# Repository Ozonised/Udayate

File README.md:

# Udayate
An open source flight controller based on STM32F411 microcontroller.

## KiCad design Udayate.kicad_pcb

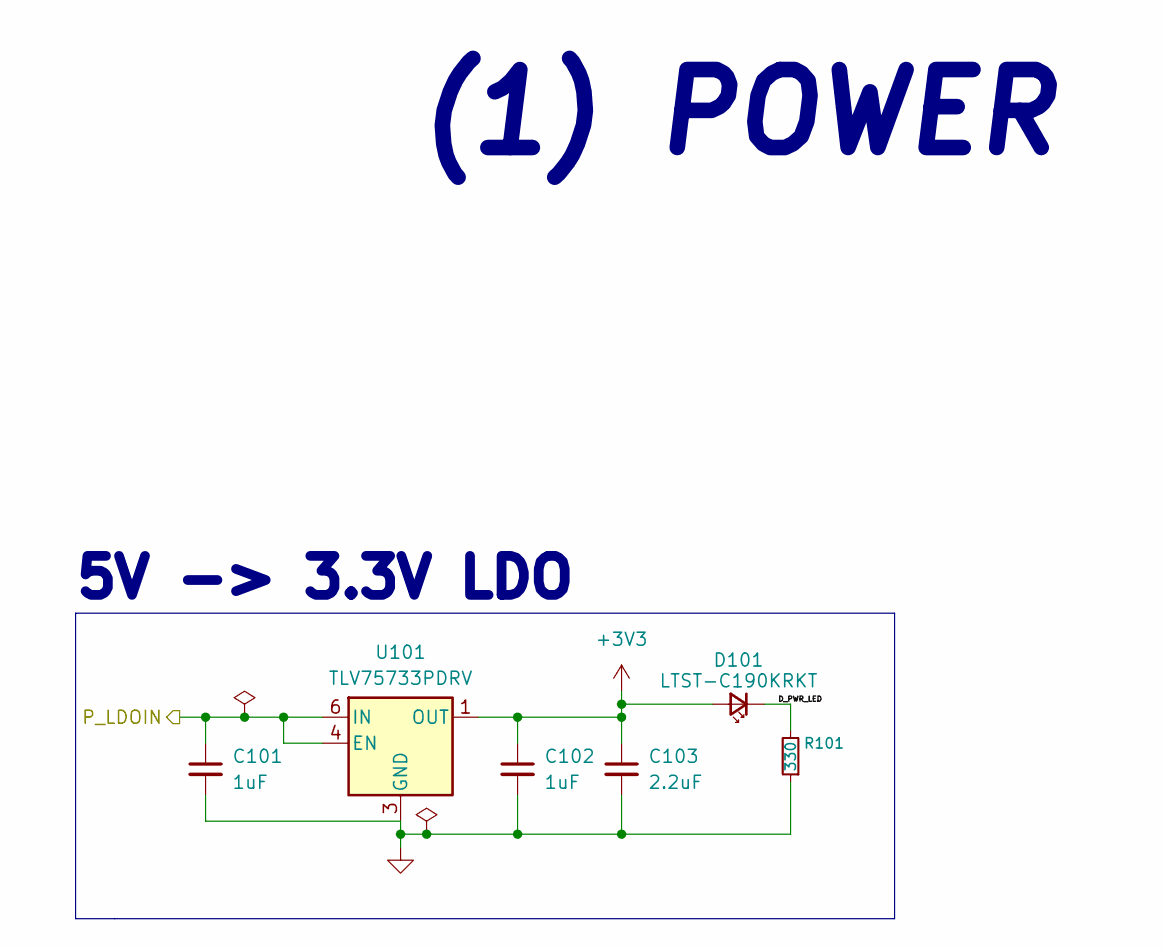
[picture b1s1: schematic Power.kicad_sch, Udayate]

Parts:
C101, C102: 1uF; C_0603_1608Metric_Pad1.08x0.95mm_HandSolder; MPN C1608X7R1V105K080AC
C103: 2.2uF; C_0805_2012Metric_Pad1.18x1.45mm_HandSolder; MPN GCM21BR71C225MA64L
D101: LTST-C190KRKT; LED_0603_1608Metric_Pad1.05x0.95mm_HandSolder; MPN LTST-C190KRKT
R101: 330; R_0603_1608Metric_Pad0.98x0.95mm_HandSolder; MPN CR0603-FX-3300ELF
U101: TLV75733PDRV; WSON-6-1EP_2x2mm_P0.65mm_EP1x1.6mm; MPN TLV75733PDRV

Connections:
+3V3: C102.1, C103.1, D101.2 (A), U101.1 (OUT); also elsewhere on the board
/IO/P_LDOIN: C101.1, U101.4 (EN), U101.6 (IN); also elsewhere on the board
/Power/D_PWR_LED: D101.1 (K), R101.2
GND: C101.2, C102.2, C103.2, R101.1, U101.3 (GND), U101.7 (GND); also elsewhere on the board

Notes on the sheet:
(1) POWER
5V -> 3.3V LDO

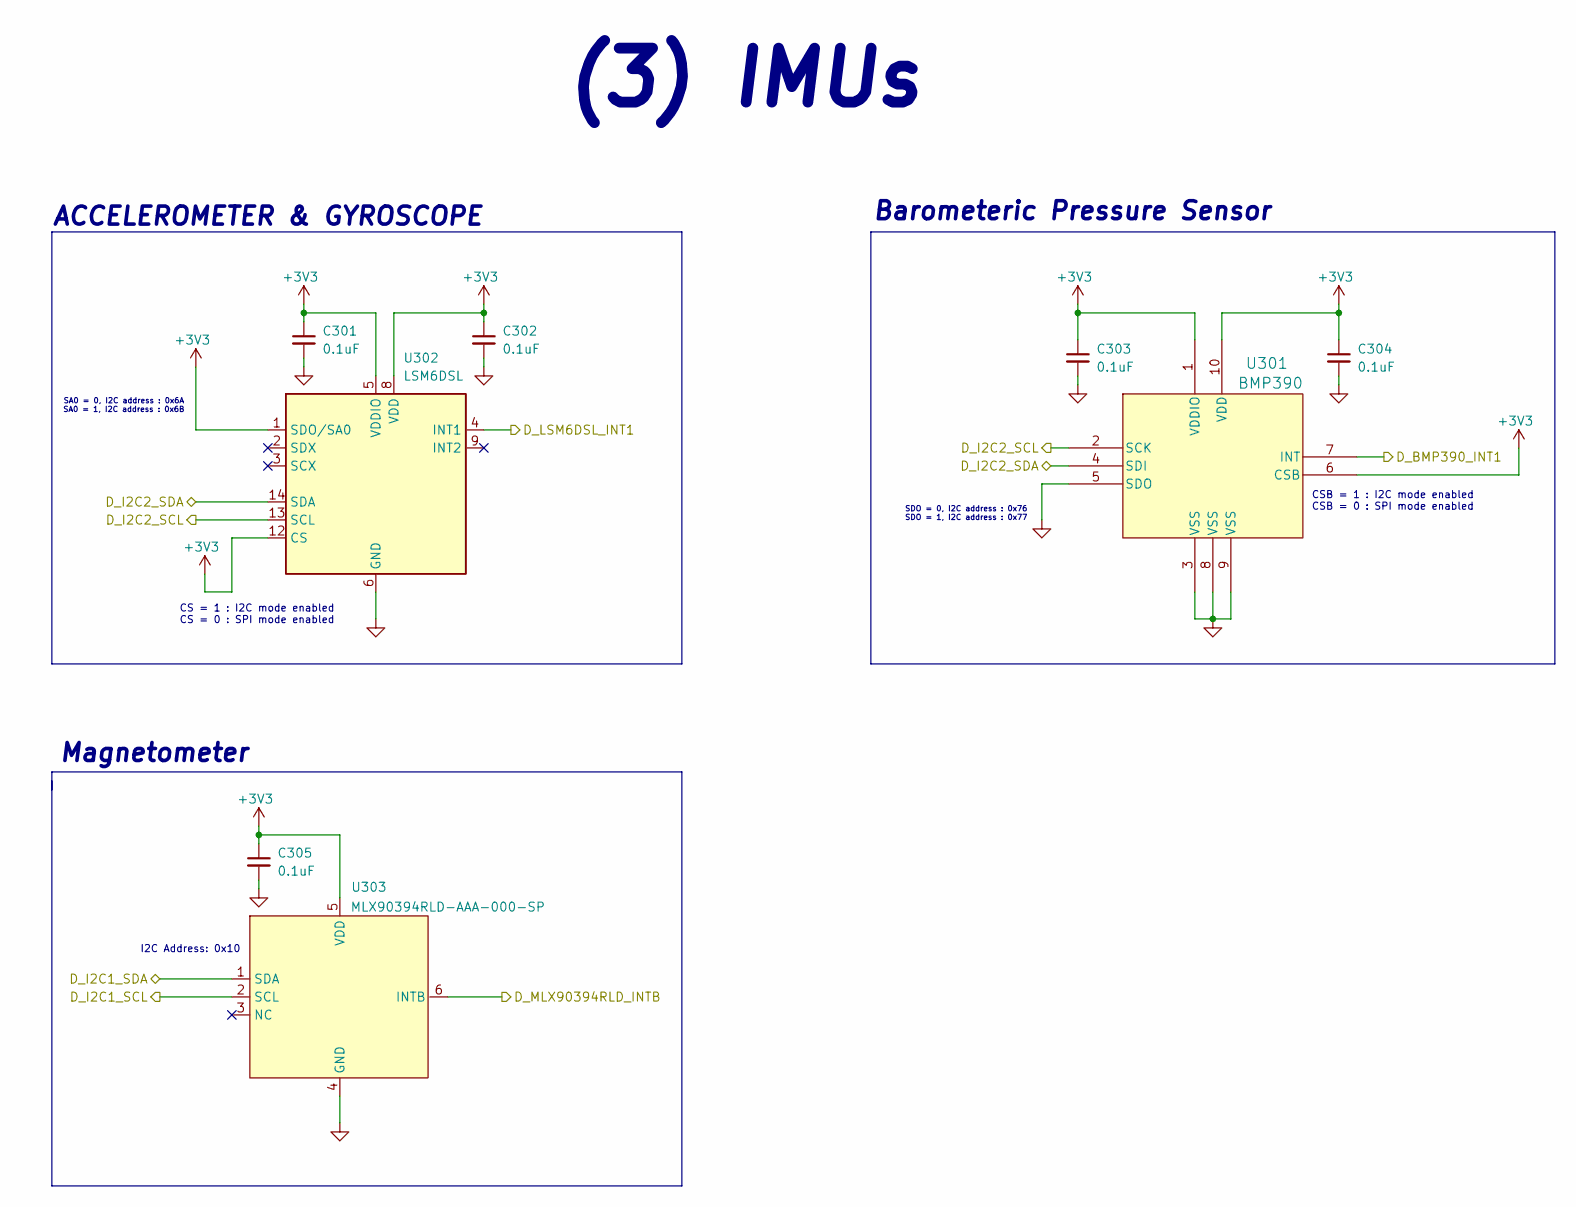
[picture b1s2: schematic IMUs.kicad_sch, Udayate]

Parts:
C301, C302, C303, C304, C305: 0.1uF; C_0603_1608Metric_Pad1.08x0.95mm_HandSolder; MPN C1608X5R1H104K080AA
U301: BMP390; 10LGA_2X2X0p75_BOS; MPN BMP390
U302: LSM6DSL; LGA-14_3x2.5mm_P0.5mm_LayoutBorder3x4y; MPN LSM6DSL
U303: MLX90394RLD-AAA-000-SP; MLX90394RLD; MPN MLX90394RLD-AAA-000-SP

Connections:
+3V3: C301.1, C302.1, C303.1, C304.1, C305.1, U301.1 (VDDIO), U301.6 (CSB), U301.10 (VDD), U302.1 (SDO/SA0), U302.5 (VDDIO), U302.8 (VDD), U302.12 (CS), U303.5 (VDD); also elsewhere on the board
/IMUs/D_BMP390_INT1: U301.7 (INT); also elsewhere on the board
/IMUs/D_I2C1_SCL: U303.2 (SCL); also elsewhere on the board
/IMUs/D_I2C1_SDA: U303.1 (SDA); also elsewhere on the board
/IMUs/D_I2C2_SCL: U301.2 (SCK), U302.13 (SCL); also elsewhere on the board
/IMUs/D_I2C2_SDA: U301.4 (SDI), U302.14 (SDA); also elsewhere on the board
/IMUs/D_LSM6DSL_INT1: U302.4 (INT1); also elsewhere on the board
/IMUs/D_MLX90394RLD_INTB: U303.6 (INTB); also elsewhere on the board
GND: C301.2, C302.2, C303.2, C304.2, C305.2, U301.3 (VSS), U301.5 (SDO), U301.8 (VSS), U301.9 (VSS), U302.6 (GND), U302.7 (GND), U303.4 (GND); also elsewhere on the board

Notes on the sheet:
CSB = 1 : I2C mode enabled CSB = 0 : SPI mode enabled
(3) IMUs
Magnetometer
SDO = 0, I2C address : 0x76 SDO = 1, I2C address : 0x77
SA0 = 0, I2C address : 0x6A SA0 = 1, I2C address : 0x6B
CS = 1 : I2C mode enabled CS = 0 : SPI mode enabled
I2C Address: 0x10
Barometeric Pressure Sensor
ACCELEROMETER & GYROSCOPE

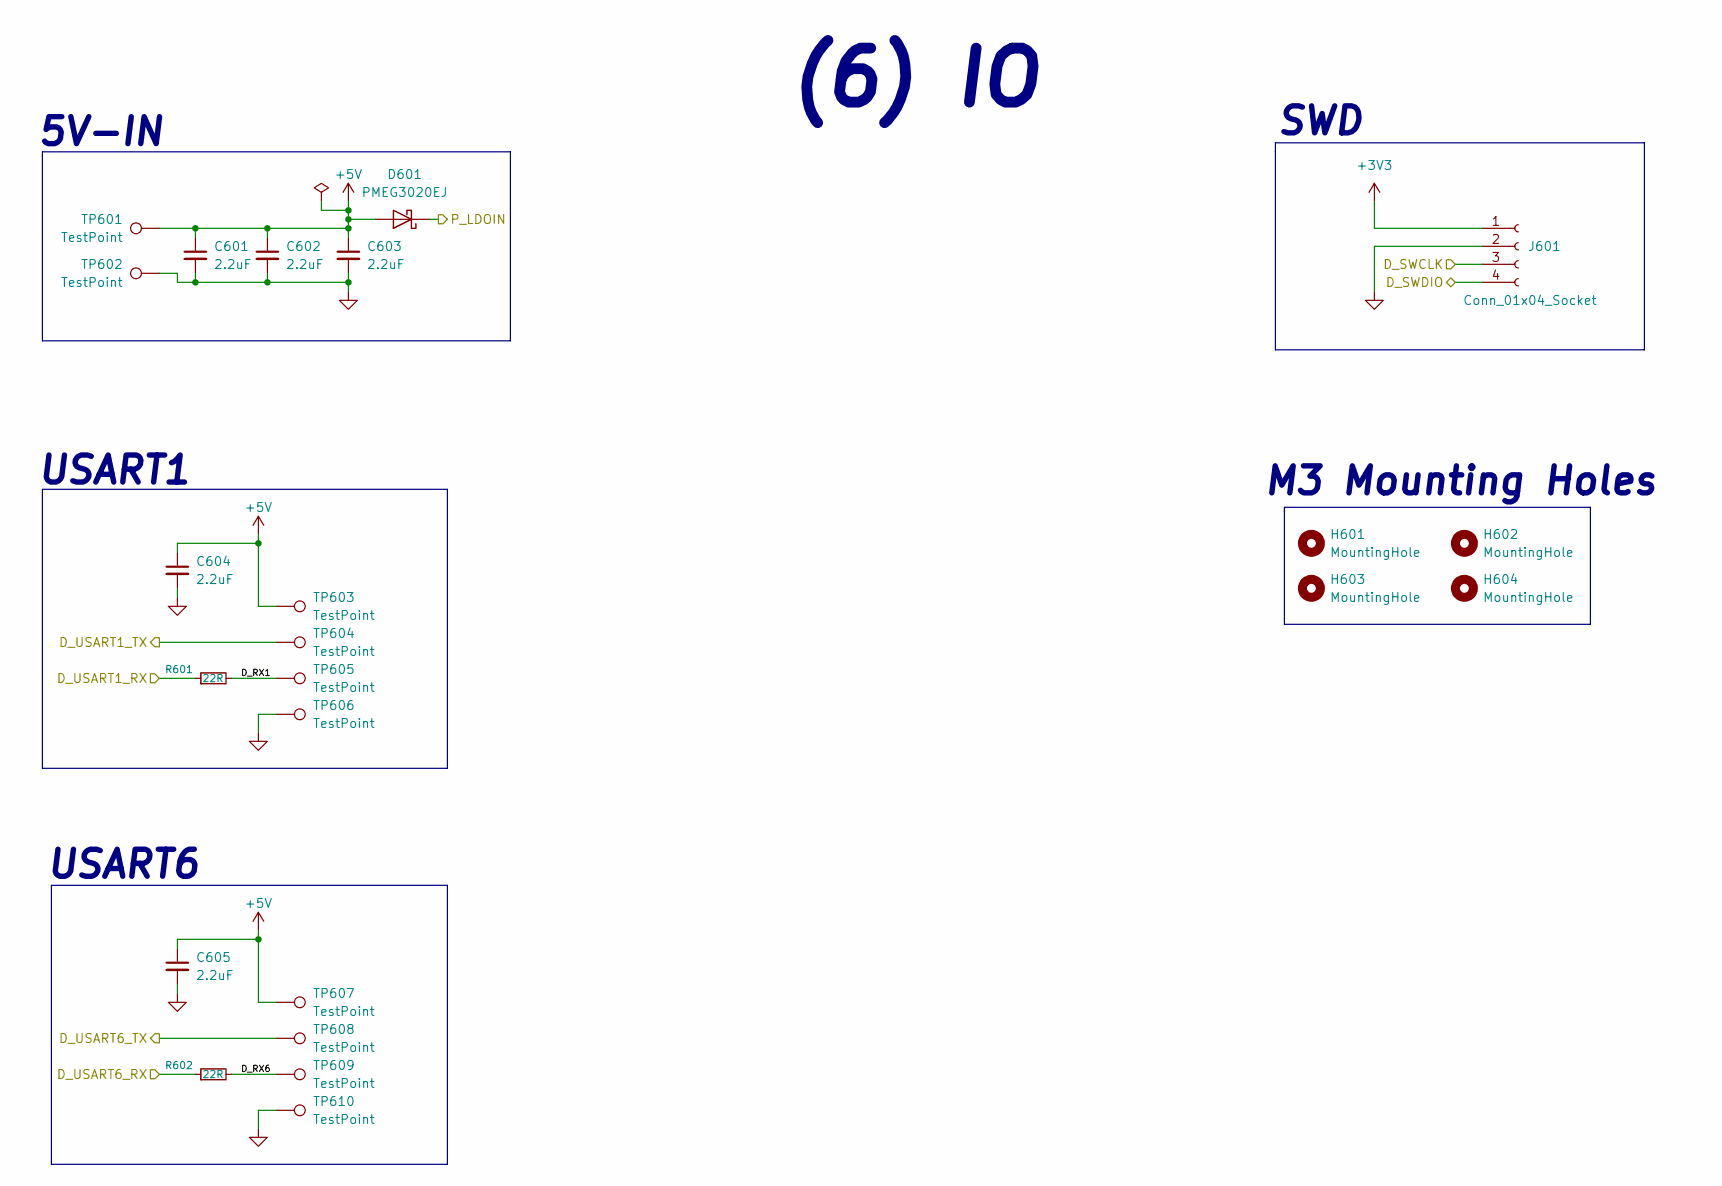
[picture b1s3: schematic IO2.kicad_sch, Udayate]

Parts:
C601, C602, C603, C604, C605: 2.2uF; C_0805_2012Metric_Pad1.18x1.45mm_HandSolder; MPN GCM21BR71C225MA64L
D601: PMEG3020EJ; D_SOD-323F; MPN PMEG3020EJ,115
H601, H602, H603, H604: MountingHole; MountingHole_3.2mm_M3
J601: Conn_01x04_Socket; PinHeader_1x04_P2.54mm_Vertical
R601, R602: 22R; R_0603_1608Metric_Pad0.98x0.95mm_HandSolder; MPN CR0603-FX-22R0ELF
TP601, TP602: TestPoint; TestPoint_Pad_2.0x2.0mm
TP603, TP604, TP605, TP606, TP607, TP608, TP609, TP610: TestPoint; TestPoint_Pad_1.0x1.0mm

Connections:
+3V3: J601.1; also elsewhere on the board
+5V: C601.1, C602.1, C603.1, C604.1, C605.1, D601.2 (A), TP601.1, TP603.1, TP607.1; also elsewhere on the board
/IO2/D_RX1: R601.2, TP605.1
/IO2/D_RX6: R602.2, TP609.1
/IO2/D_SWCLK: J601.3; also elsewhere on the board
/IO2/D_SWDIO: J601.4; also elsewhere on the board
/IO2/D_USART1_RX: R601.1; also elsewhere on the board
/IO2/D_USART1_TX: TP604.1; also elsewhere on the board
/IO2/D_USART6_RX: R602.1; also elsewhere on the board
/IO2/D_USART6_TX: TP608.1; also elsewhere on the board
/IO/P_LDOIN: D601.1 (K); also elsewhere on the board
GND: C601.2, C602.2, C603.2, C604.2, C605.2, J601.2, TP602.1, TP606.1, TP610.1; also elsewhere on the board

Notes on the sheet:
5V-IN
USART1
(6) IO
SWD
USART6
M3 Mounting Holes

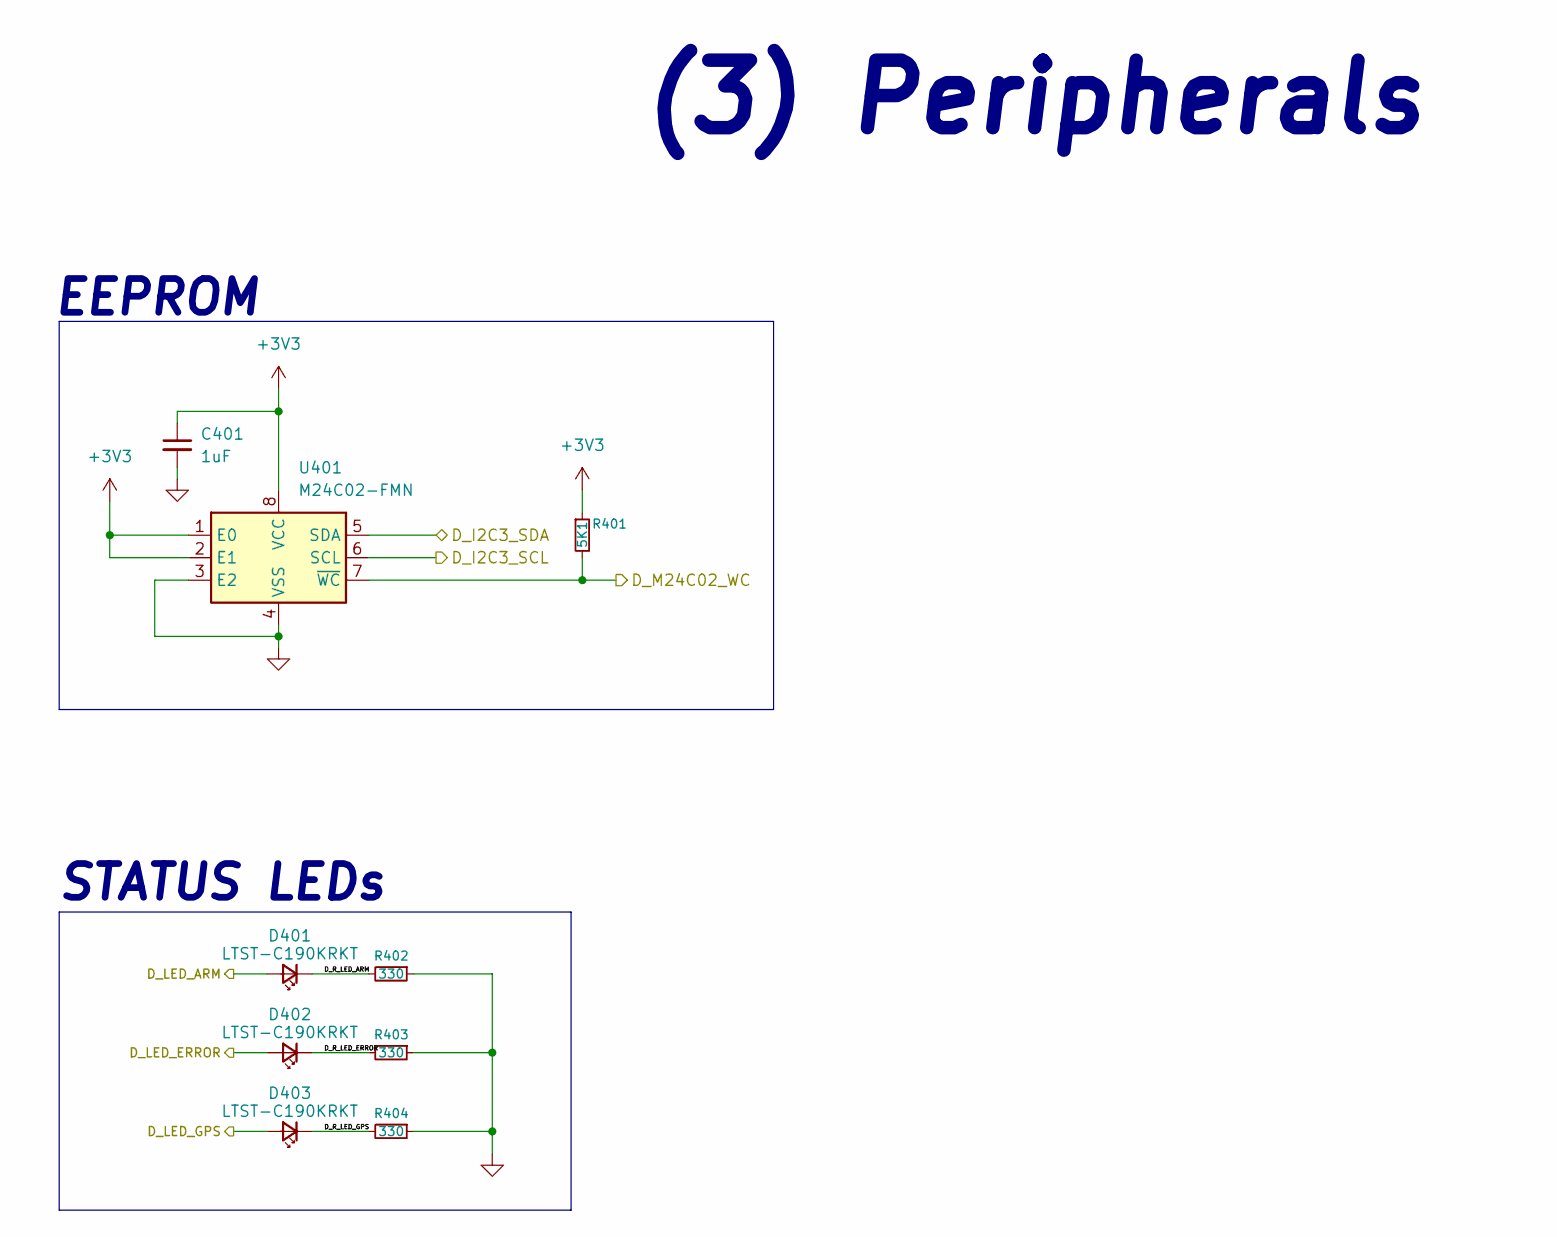
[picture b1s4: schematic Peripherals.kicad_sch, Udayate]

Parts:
C401: 1uF; C_0603_1608Metric_Pad1.08x0.95mm_HandSolder; MPN C1608X7R1V105K080AC
D401, D402, D403: LTST-C190KRKT; LED_0603_1608Metric_Pad1.05x0.95mm_HandSolder; MPN LTST-C190KRKT
R401: 5K1; R_0603_1608Metric_Pad0.98x0.95mm_HandSolder; MPN CR0603-FX-5101ELF
R402, R403, R404: 330; R_0603_1608Metric_Pad0.98x0.95mm_HandSolder; MPN CR0603-FX-3300ELF
U401: M24C02-FMN; SOIC-8_3.9x4.9mm_P1.27mm; MPN M24C02-FMN6TP

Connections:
+3V3: C401.1, R401.1, U401.1 (E0), U401.2 (E1), U401.8 (VCC); also elsewhere on the board
/MCU/D_I2C3_SCL: U401.6 (SCL); also elsewhere on the board
/MCU/D_I2C3_SDA: U401.5 (SDA); also elsewhere on the board
/MCU/D_LED_ARM: D401.2 (A); also elsewhere on the board
/MCU/D_LED_ERROR: D402.2 (A); also elsewhere on the board
/MCU/D_LED_GPS: D403.2 (A); also elsewhere on the board
/MCU/D_M24C02_WC: R401.2, U401.7 (~WC); also elsewhere on the board
/Peripherals/D_R_LED_ARM: D401.1 (K), R402.2
/Peripherals/D_R_LED_ERROR: D402.1 (K), R403.2
/Peripherals/D_R_LED_GPS: D403.1 (K), R404.2
GND: C401.2, R402.1, R403.1, R404.1, U401.3 (E2), U401.4 (VSS); also elsewhere on the board

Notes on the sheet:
(3) Peripherals
STATUS LEDs
EEPROM

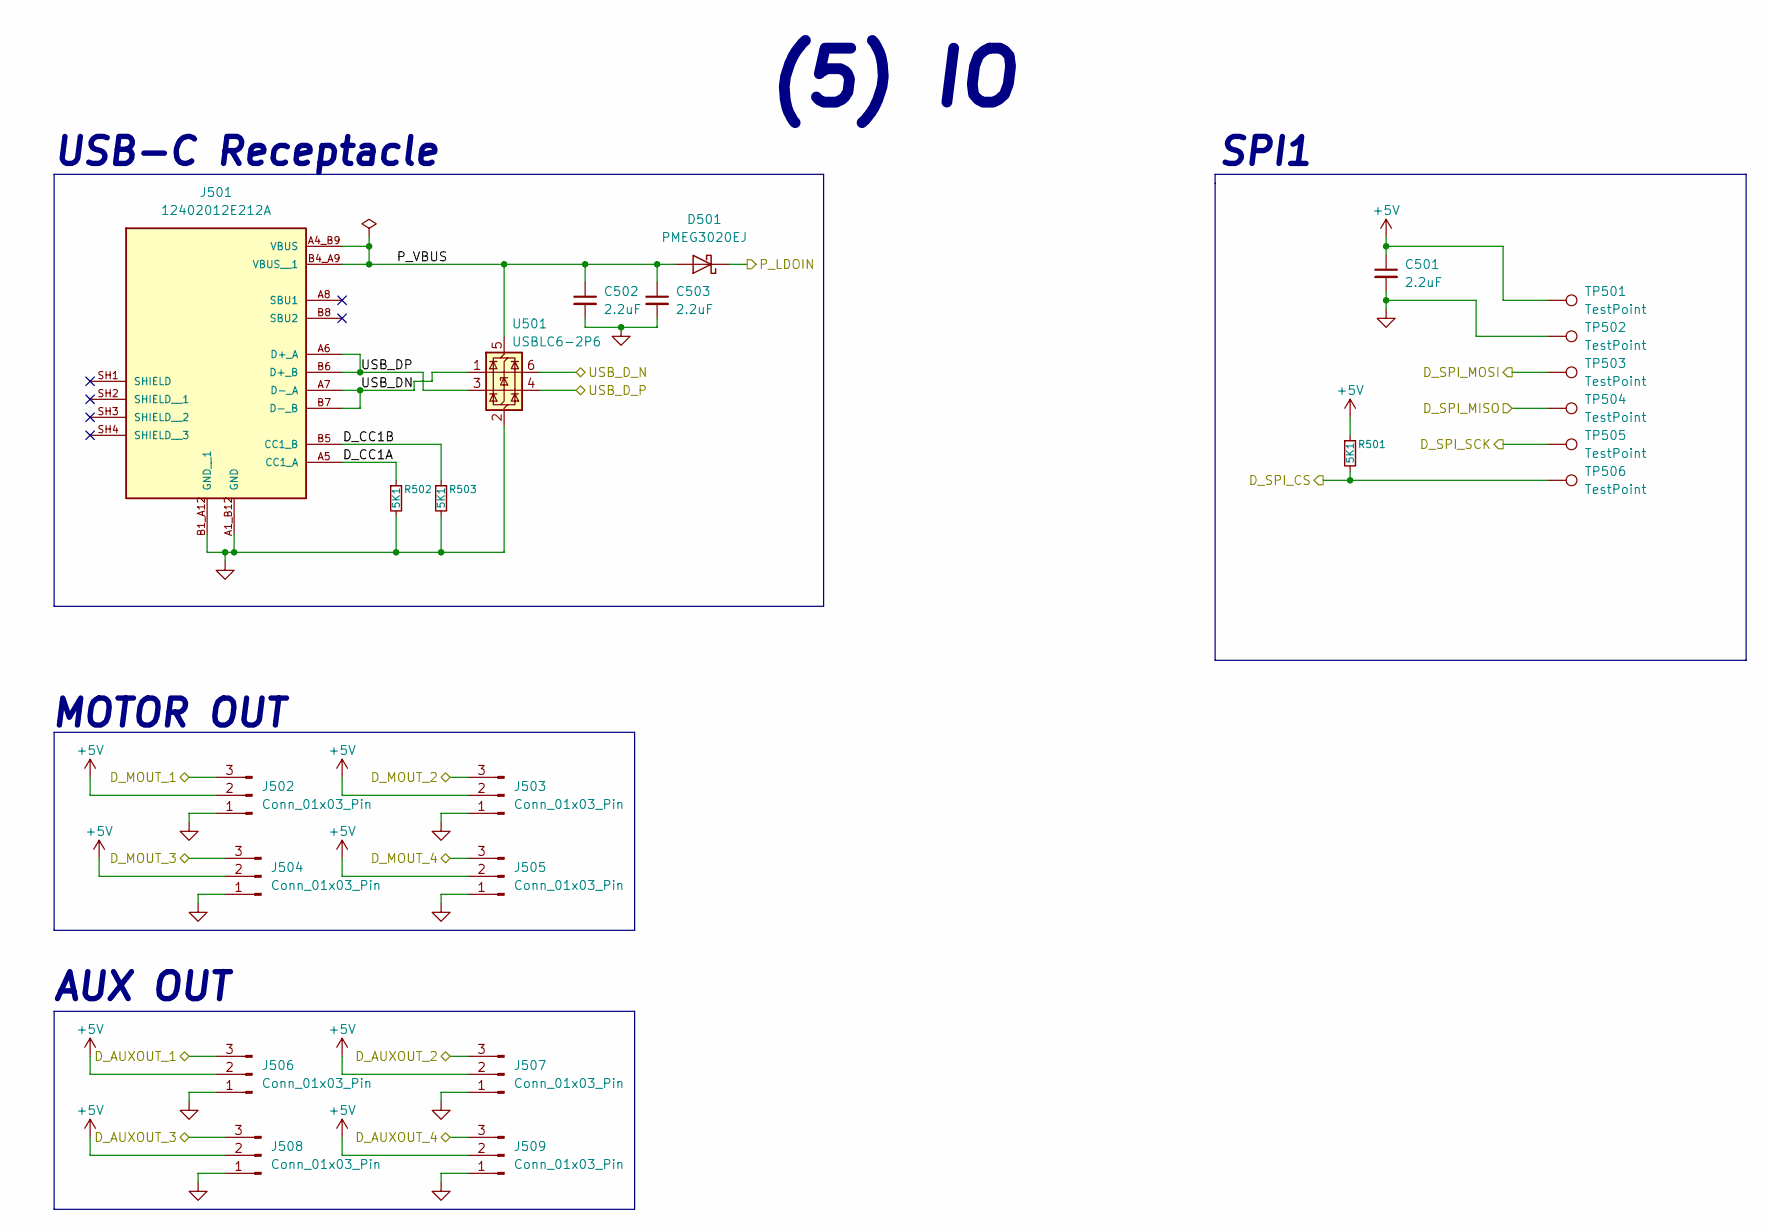
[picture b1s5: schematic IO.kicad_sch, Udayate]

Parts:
C501, C502, C503: 2.2uF; C_0805_2012Metric_Pad1.18x1.45mm_HandSolder; MPN GCM21BR71C225MA64L
D501: PMEG3020EJ; D_SOD-323F; MPN PMEG3020EJ,115
J501: 12402012E212A; AMPHENOL_12402012E212A; PARTREV 4
J502, J503, J504, J505, J506, J507, J508, J509: Conn_01x03_Pin; PinHeader_1x03_P2.54mm_Vertical
R501, R502, R503: 5K1; R_0603_1608Metric_Pad0.98x0.95mm_HandSolder; MPN CR0603-FX-5101ELF
TP501, TP502, TP503, TP504, TP505, TP506: TestPoint; TestPoint_Pad_1.0x1.0mm
U501: USBLC6-2P6; SOT-666

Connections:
+5V: C501.1, J502.2, J503.2, J504.2, J505.2, J506.2, J507.2, J508.2, J509.2, R501.1, TP501.1; also elsewhere on the board
/IO/D_AUXOUT_1: J506.3; also elsewhere on the board
/IO/D_AUXOUT_2: J507.3; also elsewhere on the board
/IO/D_AUXOUT_3: J508.3; also elsewhere on the board
/IO/D_AUXOUT_4: J509.3; also elsewhere on the board
/IO/D_CC1A: J501.A5 (CC1_A), R502.1
/IO/D_CC1B: J501.B5 (CC1_B), R503.1
/IO/D_MOUT_1: J502.3; also elsewhere on the board
/IO/D_MOUT_2: J503.3; also elsewhere on the board
/IO/D_MOUT_3: J504.3; also elsewhere on the board
/IO/D_MOUT_4: J505.3; also elsewhere on the board
/IO/D_SPI_CS: R501.2, TP506.1; also elsewhere on the board
/IO/D_SPI_MISO: TP504.1; also elsewhere on the board
/IO/D_SPI_MOSI: TP503.1; also elsewhere on the board
/IO/D_SPI_SCK: TP505.1; also elsewhere on the board
/IO/P_LDOIN: D501.1 (K); also elsewhere on the board
/IO/P_VBUS: C502.1, C503.1, D501.2 (A), J501.A4_B9 (VBUS), J501.B4_A9 (VBUS__1), U501.5 (VBUS)
/IO/USB_DN: J501.A7 (D-_A), J501.B7 (D-_B), U501.1 (I/O1)
/IO/USB_DP: J501.A6 (D+_A), J501.B6 (D+_B), U501.3 (I/O2)
/IO/USB_D_N: U501.6 (I/O1); also elsewhere on the board
/IO/USB_D_P: U501.4 (I/O2); also elsewhere on the board
GND: C501.2, C502.2, C503.2, J501.A1_B12 (GND), J501.B1_A12 (GND__1), J502.1, J503.1, J504.1, J505.1, J506.1, J507.1, J508.1, J509.1, R502.2, R503.2, TP502.1, U501.2 (GND); also elsewhere on the board

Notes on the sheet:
MOTOR OUT
SPI1
USB-C Receptacle
(5) IO
AUX OUT

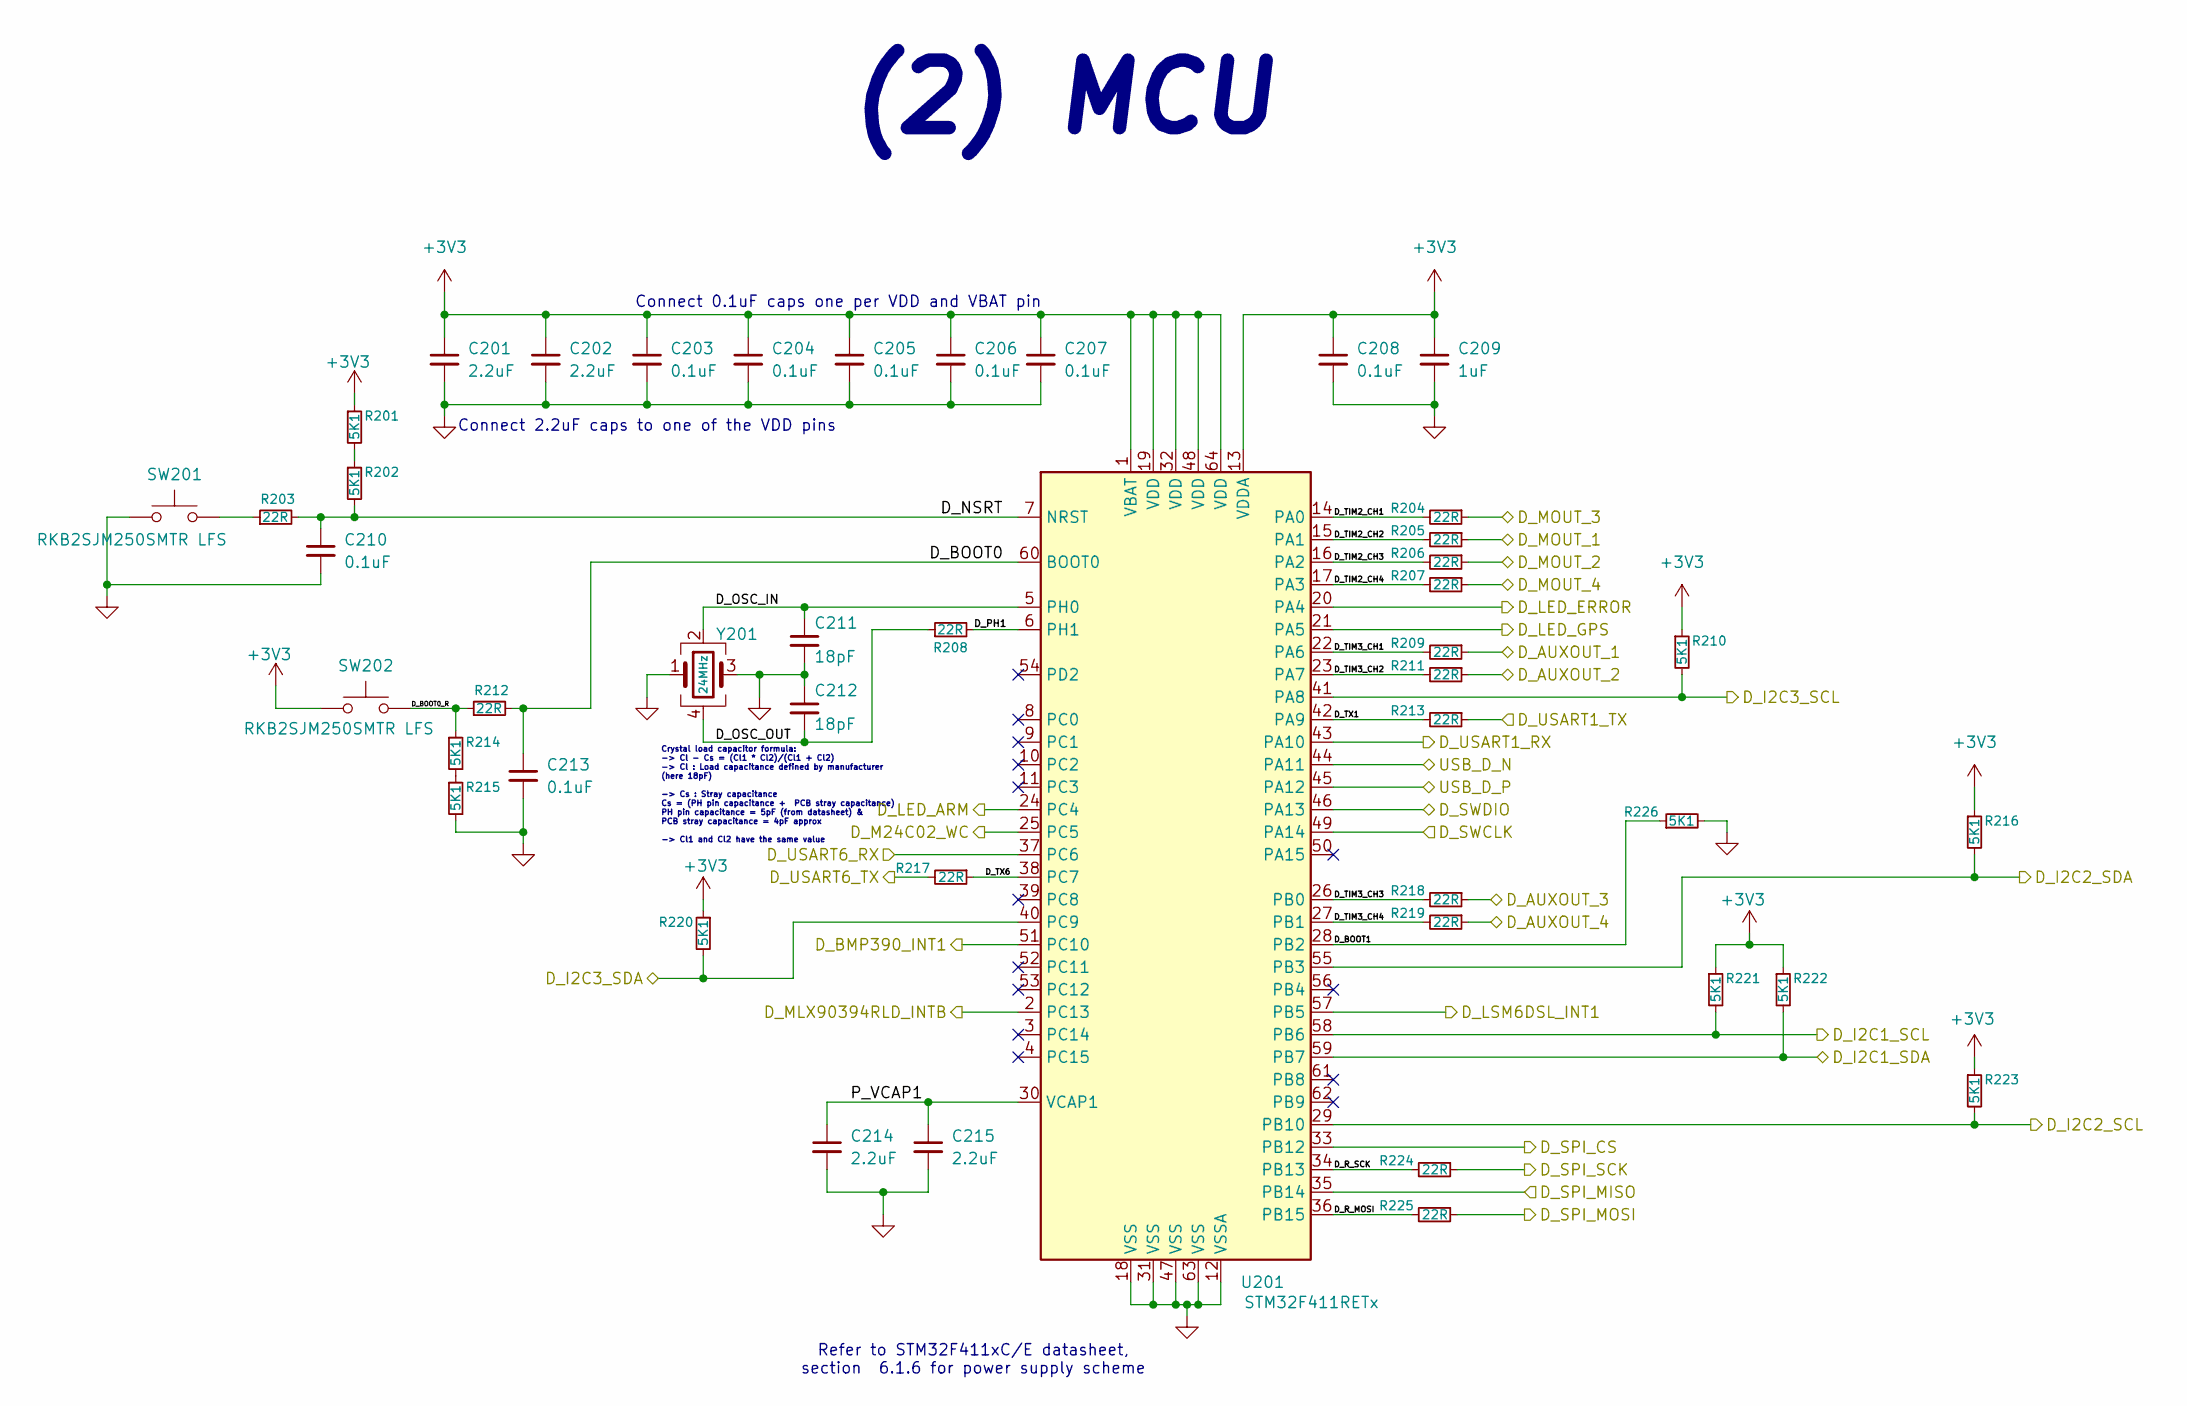
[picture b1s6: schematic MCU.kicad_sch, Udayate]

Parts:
C201, C202, C214, C215: 2.2uF; C_0805_2012Metric_Pad1.18x1.45mm_HandSolder; MPN GCM21BR71C225MA64L
C203, C204, C205, C206, C207, C208, C210, C213: 0.1uF; C_0603_1608Metric_Pad1.08x0.95mm_HandSolder; MPN C1608X5R1H104K080AA
C209: 1uF; C_0603_1608Metric_Pad1.08x0.95mm_HandSolder; MPN C1608X7R1V105K080AC
C211, C212: 18pF; C_0603_1608Metric_Pad1.08x0.95mm_HandSolder; MPN 06035A180JAT4A
R201, R202, R210, R214, R215, R216, R220, R221, R222, R223, R226: 5K1; R_0603_1608Metric_Pad0.98x0.95mm_HandSolder; MPN CR0603-FX-5101ELF
R203, R204, R205, R206, R207, R208, R209, R211, R212, R213, R217, R218, R219, R224, R225: 22R; R_0603_1608Metric_Pad0.98x0.95mm_HandSolder; MPN CR0603-FX-22R0ELF
SW201, SW202: RKB2SJM250SMTR LFS; SW_SPST_PTS810; MPN RKB2SJM250SMTR LFS
U201: STM32F411RETx; LQFP-64_10x10mm_P0.5mm; MPN STM32F411RET6
Y201: 24MHz; Crystal_SMD_3225-4Pin_3.2x2.5mm_HandSoldering; MPN ABM8-24.000MHZ-D4Y-T

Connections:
+3V3: C201.1, C202.1, C203.1, C204.1, C205.1, C206.1, C207.1, C208.1, C209.1, R201.1, R210.1, R216.1, R220.1, R221.1, R222.1, R223.1, SW202.1, U201.1 (VBAT), U201.13 (VDDA), U201.19 (VDD), U201.32 (VDD), U201.48 (VDD), U201.64 (VDD); also elsewhere on the board
/IMUs/D_BMP390_INT1: U201.51 (PC10); also elsewhere on the board
/IMUs/D_I2C1_SCL: R221.2, U201.58 (PB6); also elsewhere on the board
/IMUs/D_I2C1_SDA: R222.2, U201.59 (PB7); also elsewhere on the board
/IMUs/D_I2C2_SCL: R223.2, U201.29 (PB10); also elsewhere on the board
/IMUs/D_I2C2_SDA: R216.2, U201.55 (PB3); also elsewhere on the board
/IMUs/D_LSM6DSL_INT1: U201.57 (PB5); also elsewhere on the board
/IMUs/D_MLX90394RLD_INTB: U201.2 (PC13); also elsewhere on the board
/IO2/D_SWCLK: U201.49 (PA14); also elsewhere on the board
/IO2/D_SWDIO: U201.46 (PA13); also elsewhere on the board
/IO2/D_USART1_RX: U201.43 (PA10); also elsewhere on the board
/IO2/D_USART1_TX: R213.1; also elsewhere on the board
/IO2/D_USART6_RX: U201.37 (PC6); also elsewhere on the board
/IO2/D_USART6_TX: R217.2; also elsewhere on the board
/IO/D_AUXOUT_1: R209.1; also elsewhere on the board
/IO/D_AUXOUT_2: R211.1; also elsewhere on the board
/IO/D_AUXOUT_3: R218.1; also elsewhere on the board
/IO/D_AUXOUT_4: R219.1; also elsewhere on the board
/IO/D_MOUT_1: R205.1; also elsewhere on the board
/IO/D_MOUT_2: R206.1; also elsewhere on the board
/IO/D_MOUT_3: R204.1; also elsewhere on the board
/IO/D_MOUT_4: R207.1; also elsewhere on the board
/IO/D_SPI_CS: U201.33 (PB12); also elsewhere on the board
/IO/D_SPI_MISO: U201.35 (PB14); also elsewhere on the board
/IO/D_SPI_MOSI: R225.1; also elsewhere on the board
/IO/D_SPI_SCK: R224.1; also elsewhere on the board
/IO/USB_D_N: U201.44 (PA11); also elsewhere on the board
/IO/USB_D_P: U201.45 (PA12); also elsewhere on the board
/MCU/D_BOOT0: C213.1, R212.2, U201.60 (BOOT0)
/MCU/D_BOOT0_R: R212.1, R214.1, SW202.2
/MCU/D_BOOT1: R226.1, U201.28 (PB2)
/MCU/D_I2C3_SCL: R210.2, U201.41 (PA8); also elsewhere on the board
/MCU/D_I2C3_SDA: R220.2, U201.40 (PC9); also elsewhere on the board
/MCU/D_LED_ARM: U201.24 (PC4); also elsewhere on the board
/MCU/D_LED_ERROR: U201.20 (PA4); also elsewhere on the board
/MCU/D_LED_GPS: U201.21 (PA5); also elsewhere on the board
/MCU/D_M24C02_WC: U201.25 (PC5); also elsewhere on the board
/MCU/D_NSRT: C210.1, R202.2, R203.2, U201.7 (NRST)
/MCU/D_OSC_IN: C211.1, U201.5 (PH0), Y201.2
/MCU/D_OSC_OUT: C212.2, R208.1, Y201.4
/MCU/D_PH1: R208.2, U201.6 (PH1)
/MCU/D_R_MOSI: R225.2, U201.36 (PB15)
/MCU/D_R_SCK: R224.2, U201.34 (PB13)
/MCU/D_TIM2_CH1: R204.2, U201.14 (PA0)
/MCU/D_TIM2_CH2: R205.2, U201.15 (PA1)
/MCU/D_TIM2_CH3: R206.2, U201.16 (PA2)
/MCU/D_TIM2_CH4: R207.2, U201.17 (PA3)
/MCU/D_TIM3_CH1: R209.2, U201.22 (PA6)
/MCU/D_TIM3_CH2: R211.2, U201.23 (PA7)
/MCU/D_TIM3_CH3: R218.2, U201.26 (PB0)
/MCU/D_TIM3_CH4: R219.2, U201.27 (PB1)
/MCU/D_TX1: R213.2, U201.42 (PA9)
/MCU/D_TX6: R217.1, U201.38 (PC7)
/MCU/P_VCAP1: C214.1, C215.1, U201.30 (VCAP1)
GND: C201.2, C202.2, C203.2, C204.2, C205.2, C206.2, C207.2, C208.2, C209.2, C210.2, C211.2, C212.1, C213.2, C214.2, C215.2, R215.2, R226.2, SW201.1, U201.12 (VSSA), U201.18 (VSS), U201.31 (VSS), U201.47 (VSS), U201.63 (VSS), Y201.1, Y201.3; also elsewhere on the board
unnamed: R201.2, R202.1
unnamed: R203.1, SW201.2
unnamed: R214.2, R215.1

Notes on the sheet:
Connect 0.1uF caps one per VDD and VBAT pin
Refer to STM32F411xC/E datasheet, section 6.1.6 for power supply scheme
Connect 2.2uF caps to one of the VDD pins
(2) MCU
Crystal load capacitor formula: -> Cl - Cs = (Cl1 * Cl2)/(Cl1 + Cl2) -> Cl : Load capacitance defined by manufacturer (here 18pF) -> Cs : Stray capacitance Cs = (PH pin capacitance + PCB stray capacitance) PH pin capacitance = 5pF (from datasheet) & PCB stray capacitance = 4pF approx -> Cl1 and Cl2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

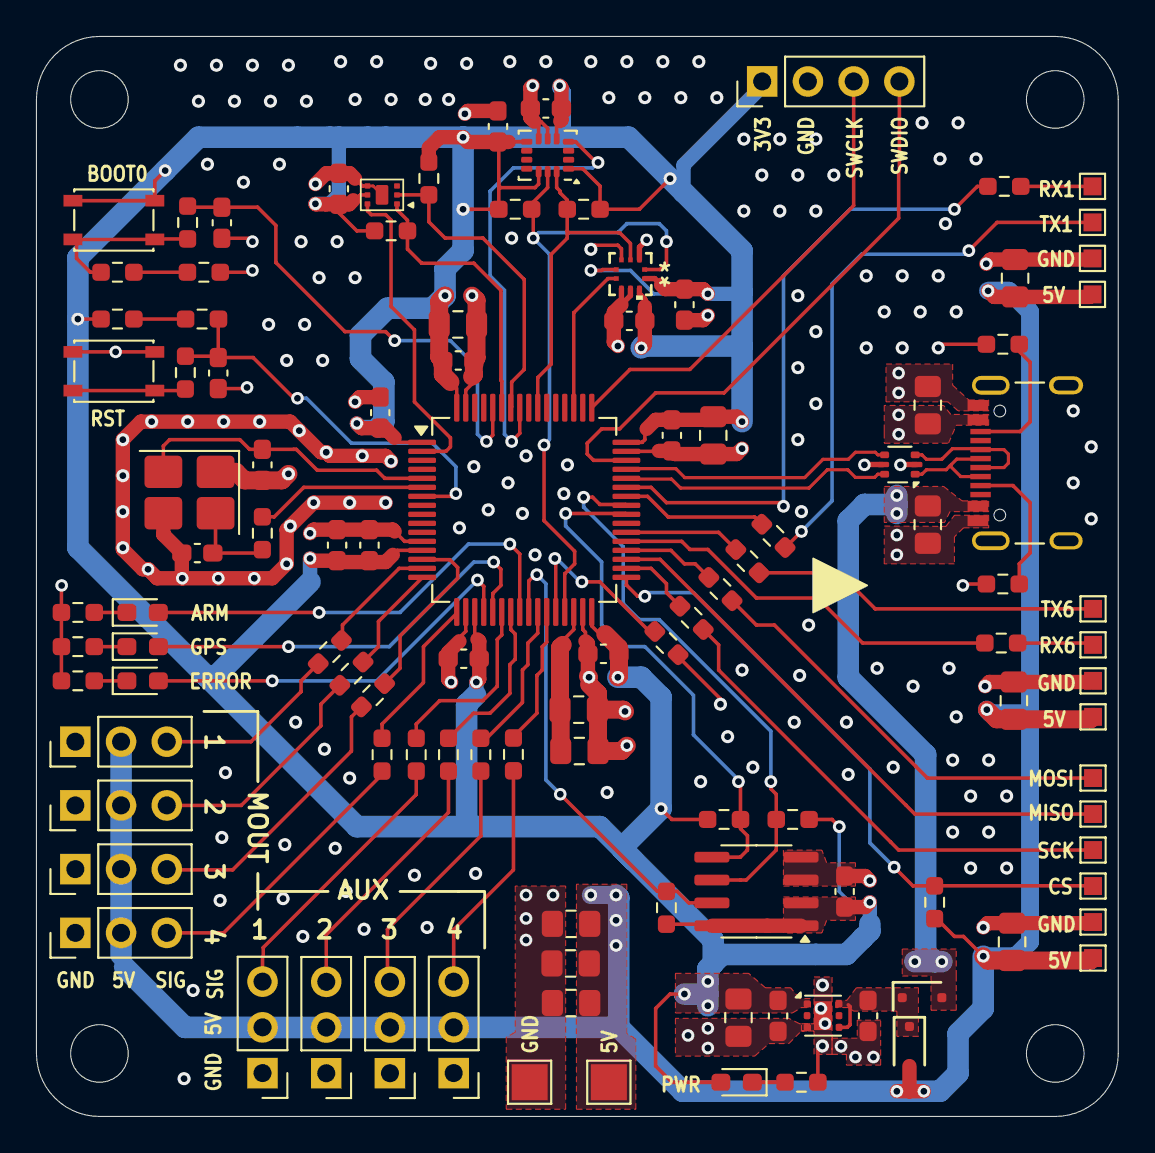
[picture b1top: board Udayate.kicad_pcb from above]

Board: 4 copper layers, 60.1 x 60.0 mm, 114 parts (0 on the bottom side), 71 nets.

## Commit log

2025-09-12 feat: add Udayate V1
2025-09-12 docs: add CERN-OHL-S-2.0 license
2025-09-12 docs; add readme
2025-09-12 docs: add board pics
2025-09-12 docs: add github repo link
2025-09-13 fix: repositioned R24 - R206 & add silk screen for 5V input
2025-09-13 fix: update gerbers to match new fixes
2025-09-13 docs: add pcb front image
2025-10-04 fix: fix magnetometer pinout
2025-10-04 fix: update rev version silkscreen on PCB
2025-10-04 fix: pin 1 marker for magnetometer
2025-10-06 docs: add ibom for assembly
2026-01-06 fix: EEPROM WC assigned to PC25
    boot1 pull down, DFU now works
2026-01-06 docs: change rev version to 1.2
2026-01-09 fix: barometer I2C address
2026-01-23 fix:mag & imu axis align
    - change mag layout
    - generate new bom
    - changed rev num

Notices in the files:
IMUs.kicad_sch:
LICENSE: CERN-OHL-S-2.0
